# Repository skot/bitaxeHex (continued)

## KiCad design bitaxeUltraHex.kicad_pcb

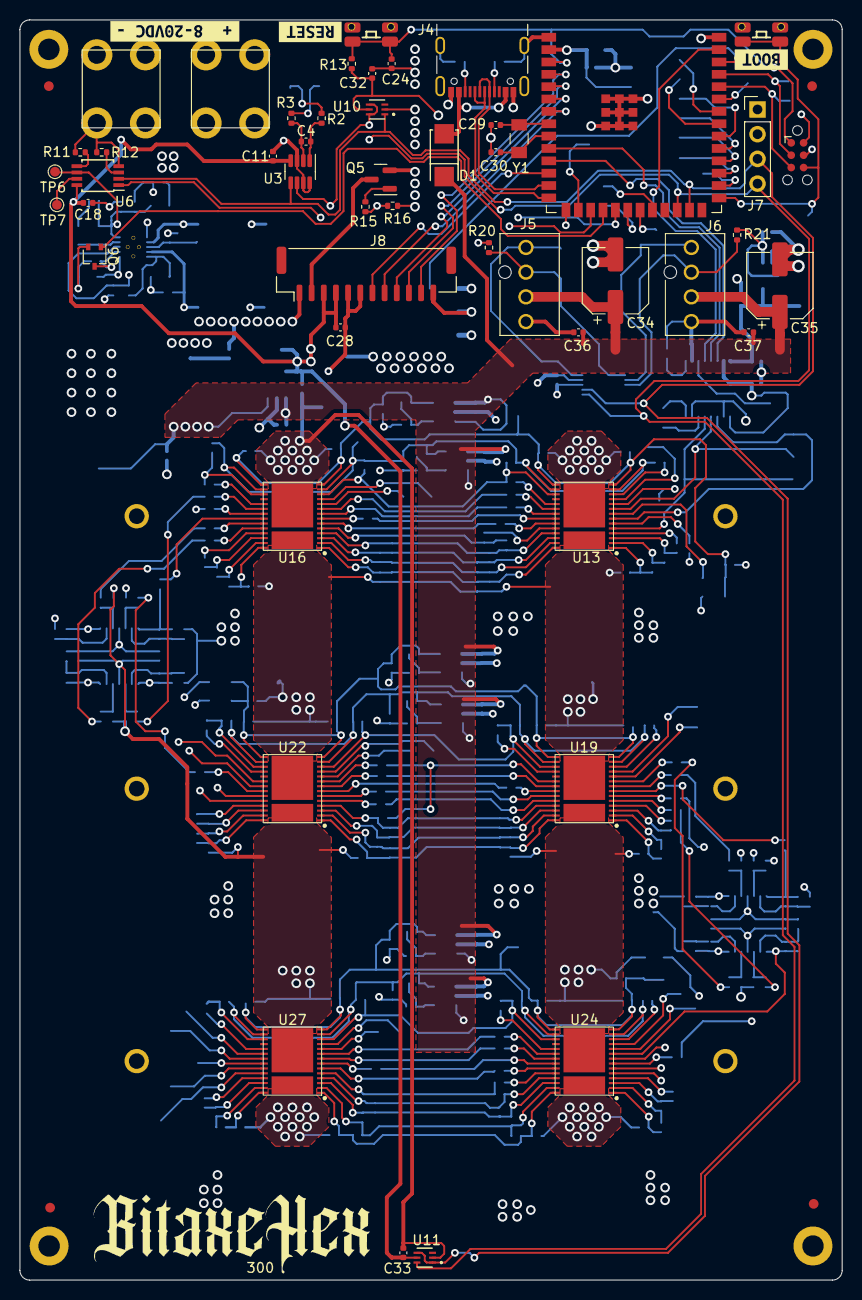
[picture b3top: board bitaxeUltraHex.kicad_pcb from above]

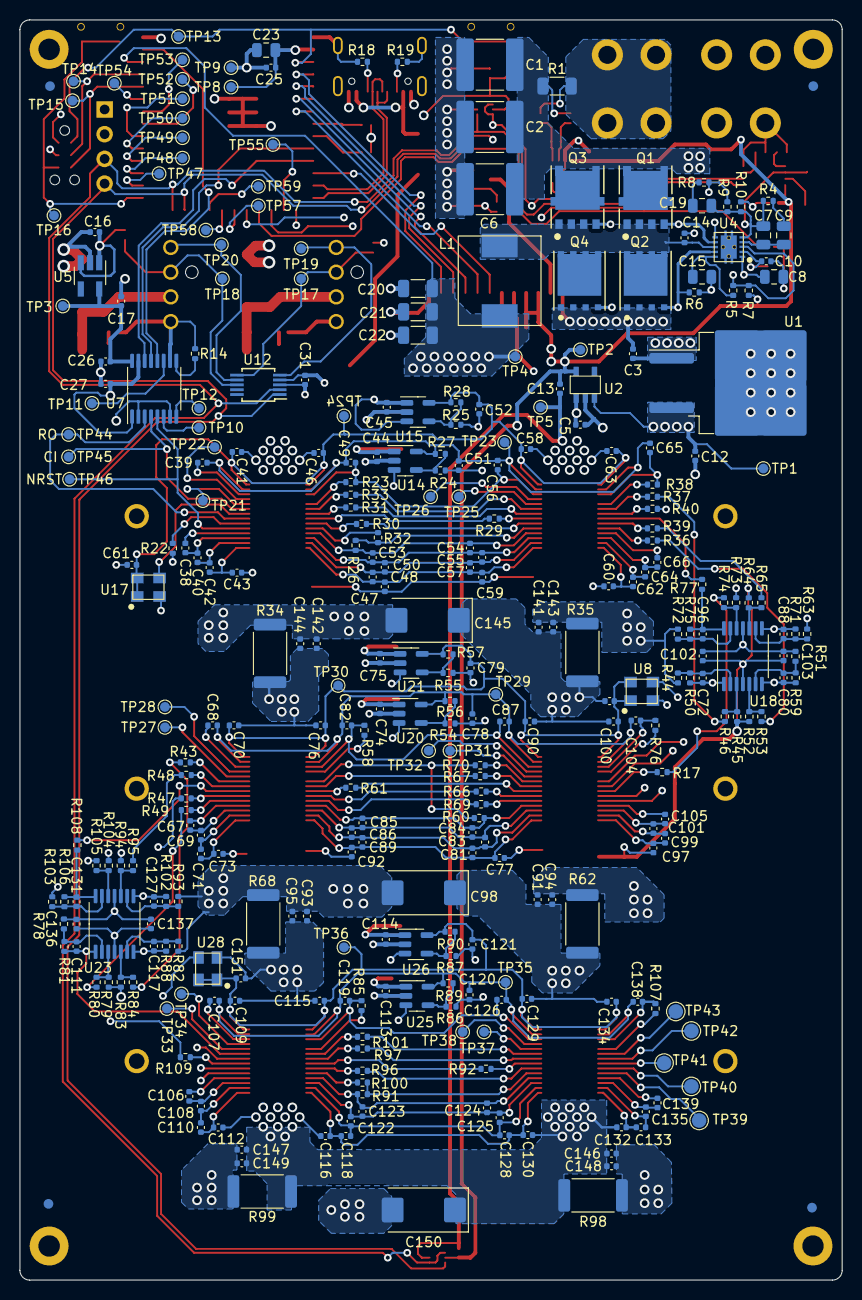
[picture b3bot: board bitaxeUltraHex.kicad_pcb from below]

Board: 4 copper layers, 84.5 x 129.5 mm, 384 parts (318 on the bottom side), 231 nets.

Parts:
C1, C2, C6: 22uF; C_2220_5650Metric
C3: 0.33uF; C_0402_1005Metric
C4: C_0402_1005Metric
C5, C11, C13, C16, C17, C18, C24, C38, C39, C40, C41, C42, C43, C46, C47, C48, C49, C50, C51, C52, C53, C54, C55, C56, C57, C58, C59, C60, C62, C63, C64, C65, C66, C67, C68, C69, C70, C71, C72, C73, C76, C77, C78, C79, C80, C81, C82, C83, C84, C85, C86, C87, C88, C89, C90, C92, C94, C95, C96, C97, C99, C100, C101, C103, C104, C105, C106, C107, C108, C109, C110, C111, C112, C115, C116, C117, C118, C119, C120, C121, C122, C123, C124, C125, C126, C127, C128, C129, C130, C131, C132, C133, C134, C135, C137, C138, C139, C143, C144, C148, C149: 1uF; C_0402_1005Metric
C7: 270pF; C_0805_2012Metric
C8: 1uF; C_0805_2012Metric
C9: 5.6nF; C_0805_2012Metric
C10: 3.3nF; C_0402_1005Metric
C12, C14, C25, C28, C44, C45, C61, C74, C75, C91, C93, C102, C113, C114, C136, C140, C141, C142, C146, C147, C151: 0.1uF; C_0402_1005Metric
C15: 4.7uF; C_0805_2012Metric
C19: 680pF; C_0805_2012Metric
C20, C21, C22: 10uF; C_1206_3216Metric
C23: 10uF; C_0805_2012Metric
C26, C27, C31, C32, C33, C36, C37: 311-3342-1-ND; C_0402_1005Metric
C29, C30: 6.8pF; C_0402_1005Metric
C34, C35: 220uF; CP_Elec_6.3x7.7
C98, C145, C150: 330uF; CP_EIA-7343-31_Kemet-D_Pad2.25x2.55mm_HandSolder
D1: SS310; SMA_L4.3-W2.6-LS5.2-RD
FID1, FID2, FID3, FID4, FID5, FID6, FID7, FID8: Fiducial; Fiducial_1mm_Mask2mm
H1, H2, H3, H4: MountingHole; 4mm_mounting
H5, H6, H7, H8, H9, H10: HeatsinkMountingHole; 2.5mm_mounting
J1: Screw Terminal; 7770-screw-terminal
J2: Conn_01x01; 7770-screw-terminal
J3: TC2030-IDC; Tag-Connect_TC2030-IDC-NL_2x03_P1.27mm_Vertical
J4: USB_C_Receptacle_USB2.0; USB_C_Receptacle_GCT_USB4105-xx-A_16P_TopMnt_Horizontal
J5, J6: Conn_01x04; 470531000
J7: Conn_01x04; PinHeader_1x04_P2.54mm_Vertical
J8: ST7789 176x320; JST_GH_BM12B-GHS-TBT_1x12-1MP_P1.25mm_Vertical
L1: 470nH; 744373580047
Q1, Q3: NTMFS5C673NLT1G
Q2, Q4: CSD17577Q5A
Q5: BSS123; SOT-23
Q6: 2N7002K; SOT-323_SC-70
R1: 2m; R_1206_3216Metric
R2, R3, R32, R36, R43, R70, R100: 0; R_0402_1005Metric
R4: 1.33k; R_0402_1005Metric
R5: 100k; R_0402_1005Metric
R6: 6.49k; R_0402_1005Metric
R7, R9, R13, R16, R22: 10k; R_0402_1005Metric
R8: 487; R_0402_1005Metric
R10: 1.54k; R_0402_1005Metric
R11: 80k; R_0402_1005Metric
R12: DNP; R_0402_1005Metric
R14: 20K; R_0402_1005Metric
R15: 1k; R_0402_1005Metric
R17, R29, R30, R31, R33, R37, R39, R40, R47, R48, R49, R61, R66, R67, R69, R92, R96, R97, R101, R109: 33; R_0402_1005Metric
R18, R19: 5.1k; R_0402_1005Metric
R20, R21: 5.6k; R_0402_1005Metric
R23, R26, R38, R58, R60, R76, R85, R91, R107: 6.8k; R_0402_1005Metric
R24, R54, R86: 309K; R_0402_1005Metric
R25, R55, R87: 130K; R_0402_1005Metric
R27, R28, R56, R57, R89, R90: 182K; R_0402_1005Metric
R34, R35, R62, R68, R98, R99: 1; R_2512_6332Metric
R44, R45, R50, R51, R59, R63, R71, R72, R75, R77, R78, R81, R82, R88, R93, R102, R103, R106, R108: 1K; R_0402_1005Metric
R46, R52, R53, R64, R65, R73, R74, R79, R80, R83, R84, R94, R95, R104, R105: 10K; R_0402_1005Metric
SW1, SW2: EVQ-9P701P; EVQ9P701P-switch
TP1, TP2, TP3, TP4, TP5, TP6, TP7, TP8, TP9, TP10, TP11, TP12, TP13, TP14, TP15, TP16, TP17, TP18, TP19, TP20, TP21, TP22, TP23, TP24, TP25, TP26, TP27, TP28, TP29, TP30, TP31, TP32, TP33, TP34, TP35, TP36, TP37, TP38, TP44, TP45, TP46, TP47, TP48, TP49, TP50, TP51, TP52, TP53, TP54, TP55, TP57, TP58, TP59: TestPoint; TestPoint_Pad_D1.0mm
TP39, TP40, TP41, TP42, TP43: TestPoint; TestPoint_Pad_D1.5mm
U1: uA7805; TO-263-2
U2: RT9080-33GJ5
U3: INA219AIDCNR; SOT-23-8
U4: TPS40305
U5: MIC5504; SOT-23-5_HandSoldering
U6: DS4432U+; TSSOP-8_3x3mm_P0.65mm
U7: SN74AVC4T774; TSSOP-16_4.4x5mm_P0.65mm
U8, U17, U28: 25MHz; O 25,0-JO32-B-1V3-1-T1-LF
U9: ESP32-S3-WROOM-1; ESP32-S3-WROOM-1U
U10, U11: TMP1075; SOT5X3-6_DRL_TEX
U12: EMC2302; MSOP-10_3x3mm_P0.5mm
U13, U16, U24, U27: BM1366_mode1; BM1366
U14, U15, U20, U21, U25, U26: ADP171AUJ-R7; TSOT-23-5
U18, U23: TLV3544; TSSOP-14_4.4x5mm_P0.65mm
U19, U22: BM1366_mode0; BM1366
Y1: 32.768kHz; SC32S-7PF20PPM
kibuzzard-65356D4E: G***; kibuzzard-65356D4E
kibuzzard-65356D5C: G***; kibuzzard-65356D5C
kibuzzard-65356D44: G***; kibuzzard-65356D44

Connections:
/1V8: C17.1, C26.2, TP3.1, U5.5 (VOUT), U7.16 (VCCA)
/3V3: C11.1, C13.1, C16.1, C18.1, C23.1, C25.1, C27.1, C28.1, C31.1, C32.1, C33.1, J3.2, J7.2, J8.3, J8.4, R7.1, R13.1, R20.2, R21.2, TP2.1, TP8.1, U2.5 (VOUT), U3.4 (VS), U5.1 (VIN), U5.3 (EN), U6.8 (VCC), U7.1 (DIR1), U7.15 (VCCB), U9.2 (3V3), U9.15 (GPIO3/TOUCH3/ADC1_CH2*), U10.5 (V+), U11.5 (V+), U12.3 (VDD)
/5V: C5.1, C12.1, C34.1, C35.1, C36.1, C37.1, C44.1, C45.1, C74.1, C75.1, C113.1, C114.1, D1.1, J5.2, J6.2, TP1.1, U1.3 (OUT), U2.1 (VIN), U2.3 (EN), U14.1 (VIN), U14.3 (EN), U15.1 (VIN), U15.3 (EN), U20.1 (VIN), U20.3 (EN), U21.1 (VIN), U21.3 (EN), U25.1 (VIN), U25.3 (EN), U26.1 (VIN), U26.3 (EN)
/BM1366-1/0V8: C39.2, C49.2, C51.1, C56.2, C65.1, R27.1, TP23.1, U13.13 (VDDIO_08_0), U13.16 (VDDIO_08_1), U14.5 (VOUT), U16.13 (VDDIO_08_0), U16.16 (VDDIO_08_1)
/BM1366-1/1V2: C41.1, C46.1, C52.1, C58.1, C61.2, C63.1, R28.1, TP24.1, U13.14 (VDDIO_18_0), U13.15 (VDDIO_18_1), U15.5 (VOUT), U16.14 (VDDIO_18_0), U16.15 (VDDIO_18_1), U17.1 (EN), U17.4 (VIN)
/BM1366-1/BI1: R22.2, U13.6 (BI)
/BM1366-1/BO: R39.2, R65.1
/BM1366-1/CLKI1: U13.8 (CLKI), U17.3 (OUT)
/BM1366-1/CO: R37.2, R46.1
/BM1366-1/NRSTO: R36.2, R53.1
/BM1366-1/RI: R77.1, U16.22 (RI)
/BM1366-1/TEMP_N1_1: TP22.1, U13.11 (TEMP_N)
/BM1366-1/TEMP_N2_1: TP26.1, U16.11 (TEMP_N)
/BM1366-1/TEMP_P1_1: TP21.1, U13.10 (TEMP_P)
/BM1366-1/TEMP_P2_1: TP25.1, U16.10 (TEMP_P)
/BM1366-1/VDD1: C43.2, C47.1, C59.2, C60.1, C70.2, C74.2, C75.2, C76.2, C78.2, C79.2, C90.2, C91.2, C93.2, C94.2, C95.2, C98.2, C100.2, C136.1, C137.1, C140.1, C141.1, C142.1, C143.1, C144.1, C145.1, R34.1, R35.1, R54.1, R55.1, R62.2, R68.2, R78.2, R82.2, R93.2, R103.2, R104.1, U8.2 (GND), U13.29 (VDD), U16.29 (VDD), U19.30 (GND), U20.2 (GND), U21.2 (GND), U22.30 (GND), U23.11 (V-)
/BM1366-2/0V8: C68.2, C78.1, C82.2, C87.2, C104.1, R56.1, TP29.1, U19.13 (VDDIO_08_0), U19.16 (VDDIO_08_1), U20.5 (VOUT), U22.13 (VDDIO_08_0), U22.16 (VDDIO_08_1)
/BM1366-2/1V2: C70.1, C76.1, C79.1, C90.1, C100.1, C140.2, R57.1, TP30.1, U8.1 (EN), U8.4 (VIN), U19.14 (VDDIO_18_0), U19.15 (VDDIO_18_1), U21.5 (VOUT), U22.14 (VDDIO_18_0), U22.15 (VDDIO_18_1)
/BM1366-2/BI2: C88.2, R71.1, U18.8, U22.21 (BI)
/BM1366-2/BO: R48.2, R95.1
/BM1366-2/CI2: C72.2, R50.1, U18.1, U22.24 (CI)
/BM1366-2/CLKI1: R40.2, U8.3 (OUT), U22.23 (CLKI)
/BM1366-2/CO: R49.2, R80.1
/BM1366-2/NRSTI2: C80.2, R59.1, U18.7, U22.20 (NRSTI)
/BM1366-2/NRSTO: R43.2, R84.1
/BM1366-2/RI: R108.1, U19.7 (RI)
/BM1366-2/RO2: R17.2, R74.1
/BM1366-2/TEMP_N1_2: TP28.1, U19.11 (TEMP_N)
/BM1366-2/TEMP_N2_2: TP32.1, U22.11 (TEMP_N)
/BM1366-2/TEMP_P1_2: TP27.1, U19.10 (TEMP_P)
/BM1366-2/TEMP_P2_2: TP31.1, U22.10 (TEMP_P)
/BM1366-2/VDD2: C73.2, C77.1, C91.1, C92.2, C93.1, C94.1, C95.1, C97.1, C98.1, C102.2, C103.2, C109.2, C113.2, C114.2, C115.2, C120.2, C121.2, C129.2, C134.2, C146.2, C147.2, C148.2, C149.2, C150.2, C151.1, R45.2, R52.1, R62.1, R64.1, R68.1, R86.1, R87.1, R98.2, R99.2, U18.4 (V+), U19.29 (VDD), U22.29 (VDD), U24.30 (GND), U25.2 (GND), U26.2 (GND), U27.30 (GND), U28.2 (GND)
/BM1366-3/0V8: C107.2, C119.2, C120.1, C126.2, C138.1, R89.1, TP35.1, U24.13 (VDDIO_08_0), U24.16 (VDDIO_08_1), U25.5 (VOUT), U27.13 (VDDIO_08_0), U27.16 (VDDIO_08_1)
/BM1366-3/1V2: C109.1, C115.1, C121.1, C129.1, C134.1, C151.2, R90.1, TP36.1, U24.14 (VDDIO_18_0), U24.15 (VDDIO_18_1), U26.5 (VOUT), U27.14 (VDDIO_18_0), U27.15 (VDDIO_18_1), U28.1 (EN), U28.4 (VIN)
/BM1366-3/BI3: C127.2, R102.1, U23.8, U24.6 (BI)
/BM1366-3/BO3: TP40.1, U27.23 (BO)
/BM1366-3/CI3: C111.2, R81.1, U23.1, U24.9 (CI)
/BM1366-3/CLKI1: R47.2, U24.8 (CLKI), U28.3 (OUT)
/BM1366-3/CLKO3: TP42.1, U27.21 (CLKO)
/BM1366-3/CO3: TP43.1, U27.20 (CO)
/BM1366-3/NRSTI3: C117.2, R88.1, U23.7, U24.5 (NRSTI)
/BM1366-3/NRSTO3: TP39.1, U27.24 (NRSTO)
/BM1366-3/RI3: TP41.1, U27.22 (RI)
/BM1366-3/RO3: R105.1, R109.2
/BM1366-3/TEMP_N1_3: TP34.1, U24.11 (TEMP_N)
/BM1366-3/TEMP_N2_3: TP38.1, U27.11 (TEMP_N)
/BM1366-3/TEMP_P1_3: TP33.1, U24.10 (TEMP_P)
/BM1366-3/TEMP_P2_3: TP37.1, U27.10 (TEMP_P)
/CI: TP45.1, U7.4 (A2), U13.9 (CI)
/ESP32/ASIC_RST: U7.12 (B3), U9.39 (GPIO1/TOUCH1/ADC1_CH0)
/ESP32/EN: C24.1, J3.1, R13.2, SW1.2, TP13.1, U9.3 (EN)
/ESP32/ESP32_RX: U7.14 (B1), U9.11 (GPIO18/U1RXD/ADC2_CH7/CLK_OUT3)
/ESP32/ESP32_TX: U7.13 (B2), U9.10 (GPIO17/U1TXD/ADC2_CH6)
/ESP32/IO0: J3.6, SW2.2, TP16.1, U9.27 (GPIO0/BOOT*)
/ESP32/PWR_EN: Q6.1 (G), U9.18 (GPIO10/TOUCH10/ADC1_CH9/FSPICS0/FSPIIO4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)
/ESP32/P_RX: J3.5, TP15.1, U9.36 (U0RXD/GPIO44/CLK_OUT2)
/ESP32/P_TX: J3.3, TP14.1, U9.37 (U0TXD/GPIO43/CLK_OUT1)
/ESP32/TFT_BLK: R15.1, R16.2, U9.17 (GPIO9/TOUCH9/ADC1_CH8/FSPIHD/SUBSPIHD)
/ESP32/TFT_CS: J8.8, U9.7 (GPIO7/TOUCH7/ADC1_CH6)
/ESP32/TFT_DC: J8.7, U9.12 (GPIO8/TOUCH8/ADC1_CH7/SUBSPICS1)
/ESP32/TFT_RES: J8.11, U9.4 (GPIO4/TOUCH4/ADC1_CH3)
/ESP32/TFT_SCL: J8.9, U9.6 (GPIO6/TOUCH6/ADC1_CH5)
/ESP32/TFT_SDA: J8.10, U9.5 (GPIO5/TOUCH5/ADC1_CH4)
/ESP32/XIN32: C29.1, U9.8 (GPIO15/U0RTS/ADC2_CH4/XTAL_32K_P), Y1.1
/ESP32/XOUT32: C30.1, U9.9 (GPIO16/U0CTS/ADC2_CH5/XTAL_32K_NH5), Y1.2
/Fan/FAN1_PWM: J5.4, TP19.1, U12.5 (PWM1)
/Fan/FAN1_TACH: J5.3, R20.1, TP17.1, U12.6 (TACH1)
/Fan/FAN2_PWM: J6.4, TP20.1, U12.7 (PWM2)
/Fan/FAN2_TACH: J6.3, R21.1, TP18.1, U12.8 (TACH2)
/NRSTI: TP46.1, U7.5 (A3), U13.5 (NRSTI)
/Power/OUT0: C7.2, C19.2, R4.2, R9.2, R10.1, TP6.1, U4.5 (FB), U6.6 (OUT0)
/Power/OUT1: TP7.1, U6.7 (OUT1)
/Power/PGOOD: R5.1, R7.2, U4.3 (PGOOD), U9.19 (GPIO11/TOUCH11/ADC2_CH0/FSPID/FSPIIO5/S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)
/Power/SW: C14.2, L1.1, Q1.1, Q1.2, Q1.3 (S), Q2.5 (D), Q3.1, Q3.2, Q3.3 (S), Q4.5 (D), U4.8 (SW)
/Power/VIN: J1.1, R1.1, R2.1
/Power/VIN_M: C1.1, C2.1, C3.1, C6.1, C8.1, Q1.5 (D), Q3.5 (D), R1.2, R3.1, U1.1 (IN), U4.1 (VDD)
/RO: TP44.1, U7.3 (A1), U13.7 (RO)
/SCL: J7.3, U3.5 (SCL), U6.2 (SCL), U9.25 (GPIO48/SPICLK_N/SUBSPICLK_N_DIFF), U10.1 (SCL), U11.1 (SCL), U11.4 (A0), U12.2 (SMCLK)
/SDA: J7.4, U3.6 (SDA), U6.1 (SDA), U9.24 (GPIO47/SPICLK_P/SUBSPICLK_P_DIFF), U10.4 (A0), U10.6 (SDA), U11.6 (SDA), U12.1 (SMDATA)
/VDD: C20.1, C21.1, C22.1, C112.2, C116.1, C130.2, C132.1, C136.2, C137.2, C146.1, C147.1, C148.1, C149.1, C150.1, L1.2, R8.1, R9.1, R79.1, R83.1, R94.1, R98.1, R99.1, TP4.1, U9.38 (GPIO2/TOUCH2/ADC1_CH1), U23.4 (V+), U24.29 (VDD), U27.29 (VDD)
GND: C1.2, C2.2, C3.2, C5.2, C6.2, C8.2, C10.2, C11.2, C12.2, C13.2, C15.2, C16.2, C17.2, C18.2, C20.2, C21.2, C22.2, C23.2, C24.2, C25.2, C26.1, C27.2, C28.2, C29.2, C30.2, C31.2, C32.2, C33.2, C34.2, C35.2, C36.2, C37.2, C41.2, C44.2, C45.2, C46.2, C51.2, C52.2, C58.2, C61.1, C63.2, C102.1, C103.1, C141.2, C142.2, C143.2, C144.2, C145.2, J2.1, J3.4, J4.A1 (GND), J4.A12 (GND), J4.B1 (GND), J4.B12 (GND), J4.S1 (SHIELD), J5.1, J6.1, J7.1, J8.1, J8.5, J8.6, J8.12, Q2.1, Q2.2, Q2.3 (S), Q4.1, Q4.2, Q4.3 (S), Q5.2 (S), Q6.2 (S), R6.2, R10.2, R11.2, R12.2, R14.1, R16.1, R18.1, R19.1, R22.1, R24.1, R25.1, R34.2, R35.2, R44.2, R51.2, R63.2, R72.2, R73.1, SW1.1, SW2.1, TP5.1, TP9.1, U1.2 (GND), U2.2 (GND), U3.3 (GND), U3.7 (A0), U3.8 (A1), U4.11 (GND), U5.2 (GND), U6.4 (GND), U7.2 (DIR2), U7.7 (DIR3), U7.10 (GND), U9.1 (GND), U9.40 (GND), U9.41 (GND), U10.2 (GND), U11.2 (GND), U12.4 (GND), U13.30 (GND), U14.2 (GND), U15.2 (GND), U16.30 (GND), U17.2 (GND), U18.11 (V-)
unnamed: C9.2, R4.1
unnamed: C19.1, R8.2
unnamed: C38.1, U13.4 (VDD4_0)
unnamed: C53.2, C54.1, R26.1, U13.25 (VDD4_0), U16.4 (VDD4_0)
unnamed: C66.2, U16.25 (VDD4_0)
unnamed: C96.2, R75.1, R77.2, U18.14
unnamed: C106.1, U24.4 (VDD4_0)
unnamed: C123.2, C124.1, R91.1, U24.25 (VDD4_0), U27.4 (VDD4_0)
unnamed: C131.2, R106.1, R108.2, U23.14
unnamed: C139.2, U27.25 (VDD4_0)
unnamed: D1.2, J4.A4 (VBUS), J4.A9 (VBUS), J4.B4 (VBUS), J4.B9 (VBUS)
unnamed: J4.A5 (CC1), R18.2
unnamed: J4.B5 (CC2), R19.2
unnamed: J8.2, Q5.3 (D)
unnamed: Q1.4 (G), Q3.4 (G), U4.7 (HDRV)
unnamed: Q2.4 (G), Q4.4 (G), R6.1, U4.9 (LDRV)
unnamed: Q5.1 (G), R15.2
unnamed: C10.1, Q6.3 (D), U4.2 (EN/SS)
unnamed: C4.1, R2.2, U3.1 (IN+)
unnamed: C4.2, R3.2, U3.2 (IN-)
unnamed: C14.1, U4.6 (BOOT)
unnamed: C15.1, R5.2, U4.10 (BP)
unnamed: C7.1, C9.1, U4.4 (COMP)
unnamed: R11.1, U6.5 (FS0)
unnamed: R12.1, U6.3 (FS1)
unnamed: TP10.1, U7.6 (A4)
unnamed: TP11.1, U7.11 (B4)
unnamed: TP12.1, U7.8 (DIR4)
unnamed: R14.2, U7.9 (OE)
unnamed: TP55.1, U9.16 (*GPIO46)
unnamed: TP57.1, U9.20 (GPIO12/TOUCH12/ADC2_CH1/FSPICLK/FSPIIO6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)
unnamed: TP58.1, U9.21 (GPIO13/TOUCH13/ADC2_CH2/FSPIQ/FSPIIO7/S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)
unnamed: TP59.1, U9.22 (GPIO14/TOUCH14/ADC2_CH3/FSPIWP/FSPIDQS/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)
unnamed: J4.A7 (D-), J4.B7 (D-), U9.13 (GPIO19/U1RTS/ADC2_CH8/CLK_OUT2/USB_D-)
unnamed: J4.A6 (D+), J4.B6 (D+), U9.14 (GPIO20/U1CTS/ADC2_CH9/CLK_OUT1/USB_D+)
unnamed: TP50.1, U9.31 (GPIO38/FSPIWP/SUBSPIWP)
unnamed: TP51.1, U9.32 (MTCK/GPIO39/CLK_OUT3/SUBSPICS1)
unnamed: TP53.1, U9.34 (MTDI/GPIO41/CLK_OUT1)
unnamed: TP52.1, U9.33 (MTDO/GPIO40/CLK_OUT2)
unnamed: TP54.1, U9.35 (MTMS/GPIO42)
unnamed: TP49.1, U9.30 (SPIDQS/GPIO37/FSPIQ/SUBSPIQ)
unnamed: TP47.1, U9.28 (SPIIO6/GPIO35/FSPID/SUBSPID)
unnamed: TP48.1, U9.29 (SPIIO7/GPIO36/FSPICLK/SUBSPICLK)
unnamed: R30.1, U13.23 (BO)
unnamed: R31.1, U13.21 (CLKO)
unnamed: R33.1, U13.20 (CO)
unnamed: C39.1, U13.12 (MODEO)
unnamed: C49.1, C56.1, R23.2, U13.17 (MODE_1), U16.12 (MODEO)
unnamed: R23.1, U13.19 (NC)
unnamed: R32.1, U13.24 (NRSTO)
unnamed: R29.1, U13.22 (RI)
unnamed: C42.2, C43.1, U13.1 (VDD1_0)
unnamed: C47.2, C48.1, C57.2, C59.1, U13.28 (VDD1_1), U16.1 (VDD1_0)
unnamed: C40.2, C42.1, U13.2 (VDD2_0)
unnamed: C48.2, C50.1, C55.2, C57.1, U13.27 (VDD2_1), U16.2 (VDD2_0)
unnamed: C38.2, C40.1, U13.3 (VDD3_0)
unnamed: C50.2, C53.1, C54.2, C55.1, U13.26 (VDD3_1), U16.3 (VDD3_0)
unnamed: R24.2, R27.2, U14.4 (ADJ)
unnamed: R25.2, R28.2, U15.4 (ADJ)
unnamed: R30.2, U16.6 (BI)
unnamed: R39.1, U16.23 (BO)
unnamed: R33.2, U16.9 (CI)
unnamed: R31.2, U16.8 (CLKI)
unnamed: R40.1, U16.21 (CLKO)
unnamed: R37.1, U16.20 (CO)
unnamed: C65.2, R38.2, U16.17 (MODE_1)
unnamed: R38.1, U16.19 (NC)
unnamed: R26.2, R32.2, U16.5 (NRSTI)
unnamed: R36.1, U16.24 (NRSTO)
unnamed: R29.2, U16.7 (RO)
unnamed: C60.2, C62.1, U16.28 (VDD1_1)
unnamed: C62.2, C64.1, U16.27 (VDD2_1)
unnamed: C64.2, C66.1, U16.26 (VDD3_1)
unnamed: R45.1, R46.2, U18.3 (+)
unnamed: C72.1, R44.1, R50.2, U18.2 (-)
unnamed: R52.2, R53.2, U18.5 (+)
unnamed: C80.1, R51.1, R59.2, U18.6 (-)
unnamed: R64.2, R65.2, U18.10 (+)
unnamed: C88.1, R63.1, R71.2, U18.9 (-)
unnamed: R73.2, R74.2, U18.12 (+)
unnamed: C96.1, R72.1, R75.2, U18.13 (-)
unnamed: R67.1, U19.21 (BI)
unnamed: R48.1, U19.8 (BO)
unnamed: R69.1, U19.24 (CI)
unnamed: R66.1, U19.23 (CLKI)
unnamed: R47.1, U19.6 (CLKO)
unnamed: R49.1, U19.5 (CO)
unnamed: C68.1, U19.12 (MODEO)
unnamed: R58.1, U19.18 (MODE_0)
unnamed: C82.1, C87.1, R58.2, U19.17 (MODE_1), U22.12 (MODEO)
unnamed: R60.2, R70.1, U19.20 (NRSTI)
unnamed: R43.1, U19.9 (NRSTO)
unnamed: R61.1, U19.22 (RO)
unnamed: C71.2, C73.1, U19.1 (VDD1_0)
unnamed: C77.2, C81.1, C89.2, C92.1, U19.28 (VDD1_1), U22.1 (VDD1_0)
unnamed: C69.2, C71.1, U19.2 (VDD2_0)
unnamed: C81.2, C83.1, C86.2, C89.1, U19.27 (VDD2_1), U22.2 (VDD2_0)
unnamed: C67.2, C69.1, U19.3 (VDD3_0)
unnamed: C83.2, C84.1, C85.2, C86.1, U19.26 (VDD3_1), U22.3 (VDD3_0)
unnamed: C67.1, U19.4 (VDD4_0)
unnamed: C84.2, C85.1, R60.1, U19.25 (VDD4_1), U22.4 (VDD4_0)
unnamed: R54.2, R56.2, U20.4 (ADJ)
unnamed: R55.2, R57.2, U21.4 (ADJ)
unnamed: R67.2, U22.8 (BO)
unnamed: R66.2, U22.6 (CLKO)
unnamed: R69.2, U22.5 (CO)
unnamed: R76.2, U22.18 (MODE_0)
unnamed: C104.2, R76.1, U22.17 (MODE_1)
unnamed: R70.2, U22.9 (NRSTO)
unnamed: R61.2, U22.7 (RI)
unnamed: R17.1, U22.22 (RO)
unnamed: C97.2, C99.1, U22.28 (VDD1_1)
unnamed: C99.2, C101.1, U22.27 (VDD2_1)
unnamed: C101.2, C105.1, U22.26 (VDD3_1)
unnamed: C105.2, U22.25 (VDD4_1)
unnamed: R79.2, R80.2, U23.3 (+)
unnamed: C111.1, R78.1, R81.2, U23.2 (-)
unnamed: R83.2, R84.2, U23.5 (+)
unnamed: C117.1, R82.1, R88.2, U23.6 (-)
unnamed: R94.2, R95.2, U23.10 (+)
unnamed: C127.1, R93.1, R102.2, U23.9 (-)
unnamed: R104.2, R105.2, U23.12 (+)
unnamed: C131.1, R103.1, R106.2, U23.13 (-)
unnamed: R96.1, U24.23 (BO)
unnamed: R97.1, U24.21 (CLKO)
unnamed: R101.1, U24.20 (CO)
unnamed: C107.1, U24.12 (MODEO)
unnamed: C119.1, C126.1, R85.2, U24.17 (MODE_1), U27.12 (MODEO)
unnamed: R85.1, U24.19 (NC)
unnamed: R100.1, U24.24 (NRSTO)
unnamed: R92.1, U24.22 (RI)
unnamed: R109.1, U24.7 (RO)
unnamed: C110.2, C112.1, U24.1 (VDD1_0)
unnamed: C116.2, C118.1, C128.2, C130.1, U24.28 (VDD1_1), U27.1 (VDD1_0)
unnamed: C108.2, C110.1, U24.2 (VDD2_0)
unnamed: C118.2, C122.1, C125.2, C128.1, U24.27 (VDD2_1), U27.2 (VDD2_0)
unnamed: C106.2, C108.1, U24.3 (VDD3_0)
unnamed: C122.2, C123.1, C124.2, C125.1, U24.26 (VDD3_1), U27.3 (VDD3_0)
unnamed: R86.2, R89.2, U25.4 (ADJ)
unnamed: R87.2, R90.2, U26.4 (ADJ)
unnamed: R96.2, U27.6 (BI)
unnamed: R101.2, U27.9 (CI)
unnamed: R97.2, U27.8 (CLKI)
unnamed: C138.2, R107.2, U27.17 (MODE_1)
unnamed: R107.1, U27.19 (NC)
unnamed: R91.2, R100.2, U27.5 (NRSTI)
unnamed: R92.2, U27.7 (RO)
unnamed: C132.2, C133.1, U27.28 (VDD1_1)
unnamed: C133.2, C135.1, U27.27 (VDD2_1)
unnamed: C135.2, C139.1, U27.26 (VDD3_1)

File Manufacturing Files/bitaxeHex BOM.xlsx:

Qty | Ref Des | Value | DK | Manufacturer | PARTNO | DNP
3 | C1, C2, C6 | 22uF | 445-1655-1-ND |  | CKG57NX5R1H226M500JH
1 | C3 | 0.33uF | 490-GRM155R61J334ME01JCT-ND |  | GRM155R61J334ME01J
1 | C4 | 1uF | 587-5514-1-ND |  | EMK105BJ105MV-F | DNP
101 | C5, C11, C13, C16, C17, C18, C24, C38, C39, C40, C41, C42, C43, C46, C47, C48, 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 | 1uF | 587-5514-1-ND |  | EMK105BJ105MV-F
1 | C7 | 270pF | 399-C0805C271J5GAC7800CT-ND |  | C0805C271J5GAC7800
1 | C8 | 1uF | 1276-6471-1-ND |  | CL21B105KOFNNNG
1 | C9 | 5600pF | 445-6944-1-ND |  | CGA4C2C0G1H562J060AA
1 | C10 | 3300pF | 1276-1552-1-ND |  | CL05B332KB5NNNC
28 | C12, C14, C25, C26, C27, C28, C31, C32, C33, C36, C37, C44, C45, C61, C74, C75,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 | 0.1uF | 1292-1639-1-ND |  | 0402X104K100CT
1 | C15 | 4.7uF | 490-14466-1-ND |  | GRM21BR71C475KE51L
1 | C19 | 680pF | 311-1126-1-ND |  | CC0805KRX7R9BB681
3 | C20, C21, C22 | 10uF | 1276-6641-1-ND |  | CL31B106MOHNNNE
1 | C23 | 10uF | 1276-1096-1-ND |  | CL21A106KOQNNNE
2 | C29, C30 | 6.8pF | 399-C0402C689C5GAC7867CT-ND |  | C0402C689C5GAC7867
2 | C34, C35 | 220uF | 732-8422-1-ND |  | 865080345012
3 | C98, C145, C150 | 330uF | 718-1028-1-ND |  | 293D337X9010E2TE3
1 | D1 | SS310 | SK310A-LTPMSCT-ND |  | SK310A-LTP
1 | J1 | Screw Terminal | 36-7770-ND |  | 36-7770
1 | J2 | Conn_01x01 | A100886CT-ND |  | 63862-1
1 | J4 | USB_C_Receptacle_USB2.0 | 2073-USB4105-GF-ACT-ND |  | USB4105-GF-A
2 | J5, J6 | Conn_01x04 | WM4330-ND |  | 0470531000
1 | J8 | ST7789 176x320 | 455-BM12B-GHS-TBTCT-ND |  | BM12B-GHS-TBT
1 | L1 | 470nH | 732-7221-1-ND |  | 744373580047
2 | Q1, Q3 | NTMFS5C673NLT1G | NTMFS5C673NLT1GOSCT-ND |  | NTMFS5C673NLT1G
2 | Q2, Q4 | CSD17577Q5A | 296-39996-1-ND |  | CSD17577Q5A
1 | Q5 | BSS123 | 4530-BSS123CT-ND |  | BSS123
1 | Q6 | 2N7002K | 2N7002KWCT-ND |  | 2N7002KW
1 | R1 | 2m | 13-PA1206FRE7W0R002ZCT-ND |  | PA1206FRE7W0R002Z
5 | R2, R3, R36, R43, R70 | 0 | 311-0.0JRCT-ND |  | RC0402JR-070RL
1 | R4 | 1.33k | 311-1.33KLRCT-ND |  | RC0402FR-071K33L
1 | R5 | 100k | 311-100KJRCT-ND |  | RC0402JR-07100KL | DNP
1 | R6 | 6.49k | 311-6.49KLRCT-ND |  | RC0402FR-076K49L
20 | R7, R9, R13, R16, R22, R46, R52, R53, R64, R65, R73, R74, R79, R80, R83, R84, R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 | 10k | 311-10KJRCT-ND |  | RC0402JR-0710KL
1 | R8 | 487 | YAG2373CT-ND |  | RC0402FR-07487RL
1 | R10 | 1.54k | YAG3040CT-ND |  | RC0402FR-071K54L
1 | R11 | 80k | 311-80.6KLRCT-ND |  | RC0402FR-0780K6L
1 | R12 | DNP |  |  |  | DNP
1 | R14 | 20K | 311-20.0KLRCT-ND |  | RC0402FR-0720KL
20 | R15, R44, R45, R50, R51, R59, R63, R71, R72, R75, R77, R78, R81, R82, R88, R93,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 | 1k | 311-1.00KLRCT-ND |  | RC0402FR-071KL
20 | R17, R29, R30, R31, R33, R37, R39, R40, R47, R48, R49, R61, R66, R67, R69, R92,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 | 33 | 311-33.0LRCT-ND |  | RC0402FR-0733RL
2 | R18, R19 | 5.1k | 13-RC0402FR-135K1LCT-ND |  | RC0402FR-135K1L
2 | R20, R21 | 5.6k | 13-RC0402FR-135K6LCT-ND |  | RC0402FR-135K6L
6 | R23, R32, R38, R41, R42, R58 | 33 | 311-33.0LRCT-ND |  | RC0402FR-0733RL | DNP
3 | R24, R54, R86 | 309k 1% | YAG3108CT-ND |  | RC0402FR-07309KL
3 | R25, R55, R87 | 69.8k 1% | YAG3216CT-ND |  | RC0402FR-0769K8L
3 | R26, R60, R91 | 2k | YAG2303CT-ND |  | RT0402BRD072KL
6 | R27, R28, R56, R57, R89, R90 | 182k 1% | YAG3015CT-ND |  | RC0402FR-07182KL
6 | R34, R35, R62, R68, R98, R99 | 1 | 118-CR2512-F/-1R00ELFCT-ND |  | CR2512-F/-1R00ELF
2 | SW1, SW2 | EVQ-9P701P | P19095CT-ND | G-Switch(品赞) | EVQ-9P701P
1 | U1 | uA7805 | 296-20796-1-ND |  | UA7805CKTTR
1 | U2 | RT9080-33GJ5 | 1028-1509-1-ND |  | RT9080-33GJ5
1 | U3 | INA219AID | 296-33291-5-ND | TI(德州仪器) | INA219AID
1 | U4 | TPS40305 | 296-37445-1-ND |  | TPS40305DRCR
1 | U5 | MIC5504 | 576-4879-1-ND |  | MIC5504-1.8YM5-TR
1 | U6 | DS4432U+ | DS4432U+-ND |  | DS4432U+
1 | U7 | SN74AVC4T774 | 296-24739-1-ND |  | SN74AVC4T774PWR
3 | U8, U17, U28 | 25MHz | 1908-O250-JO32-B-1V3-1-T1-LFCT-ND |  | O 25,0-JO32-B-1V3-1-T1-LF
1 | U9 | ESP32-S3-WROOM-1 | 1965-ESP32-S3-WROOM-1U-N16R8CT-ND |  | ESP32-S3-WROOM-1U-N16R8
1 | U10 | TMP1075 | 296-TMP1075NDRLRCT-ND |  | TMP1075NDRLR
1 | U11 | TMP1075 | 296-TMP1075NDRLRCT-ND |  | TMP1075NDRLR
1 | U12 | EMC2302 | EMC2302-2-AIZL-CT-ND |  | EMC2302-2-AIZL-TR
2 | U13, U24 | BM1366_mode1
6 | U14, U15, U20, U21, U25, U26 | ADP171AUJ-R7 | 505-ADP171AUJZ-R7CT-ND |  | ADP171AUJZ-R7
2 | U16, U27 | BM1366_mode1
2 | U18, U23 | TLV3544 | 296-45352-1-ND |  | TLV3544IPWR
1 | U19 | BM1366_mode0
1 | U22 | BM1366_mode0
1 | Y1 | 32.768kHz | 728-1074-1-ND |  | SC32S-7PF20PPM

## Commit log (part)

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2023-08-22 renamed hex to ultraHex
2023-08-31 update with BM1366
2023-09-01 cleanup parts and symbol libraries. added TMP1075
2023-09-01 added EMC2302
2023-09-01 added DK and PARTNO for the fan controller and temp sensors
2023-09-11 moved all custom symbols and footprints to the bitaxe library
2023-09-11 very rough sorting and placement
2023-09-12 more rough layout work
2023-09-12 cleanup
2023-09-12 flip center asic pads
2023-09-12 alignment
2023-09-14 test file for pushing to repo
2023-09-14 Replace reference voltage regulators with new one
2023-09-15 switch voltage reference regulators to ADP170, reannotate
2023-09-15 arrange components around voltage regulators
2023-09-15 Rough draft parts placement
2023-09-15 changed USB connector to USB C. updated display.
2023-09-15 added enclosure edge cuts. added heatsink outline. changed the two middle voltage domain ASICs to mode 0 so the data lines can snake through all 6 chips.
2023-09-15 value label cleanup
2023-09-22 add level translator circuits to ASIC communications
2023-09-23 Update temperature sensors, start deep review
2023-09-24 add 1v8 LDO and consolidate voltage level translators
2023-09-25 Resolved all unconnected pins, re-annotated, reviewed for layout
2023-09-27 replace Q5 with BSS123
2023-09-28 Rough parts placement
2023-09-29 shuffle resistors
2023-09-29 more parts placement
2023-09-29 switch power/comms topology to columns and zig-zag
2023-09-29 remove unused libraries
2023-09-29 fixed part numbers and footprints on the buck reg FETs
2023-09-30 add some power planes and do some comms routing
2023-10-01 Arrange the comms voltage level translators
2023-10-01 move power resistors under ASICs
2023-10-01 add screw terminals, replace OLED display with optional connector
2023-10-02 major rework of the power supply section
2023-10-03 add 3D model of screw terminal to footprint
2023-10-04 Revert "More parts placement"
    This reverts commit 19c08c982123baf7c8f78aef6401739b38439525.
2023-10-04 more parts placement, switch to ESP32 with external antenna
2023-10-05 nearly final parts placement
2023-10-09 Routing of front end ESP32, power supply, fan controller, level translator, and programming connector
2023-10-10 shuffle resistors on RI/RO, more routing on ASICs
2023-10-12 finish routing communications
2023-10-13 add oscillators, large bypass caps, start routing reference voltages
2023-10-16 Finished routing stage 1
2023-10-16 added some models and regenerated the board render
2023-10-16 update ESP32 3d model
2023-10-16 added some DK part numbers
2023-10-17 Add ESP32 testpoints, fix all DRC errors
2023-10-19 added PWR_EN transistor
2023-10-19 switched PWR_EN to GPIO10 so that we can match this up better with ultra-v1.2
2023-10-19 removed external libraries from project settings
2023-10-19 cleaned up some DRC warnings
2023-10-22 added fiducials
2023-10-22 changed version to 300
2023-10-22 re added mounting holes and heatsink mounting holes.
2023-10-22 BOM mostly completed
2023-10-22 added BOM, schematic PDF, position file and candidate gerbers
2023-10-23 add heatsink to library and PCB render
2023-10-23 rename project file to "bitaxeHex". remove old gerbers
2023-10-23 pull in updated TPS40305 footprint
2023-10-23 link heatsink to schematic and re-link heatsink mounting holes :P
2023-10-23 silkscreen cleanup
2023-10-24 fix D1 part numbers
2023-10-24 U10,U11 BOM fix
2023-10-24 a little less paste on the BM1366 power pads
2023-10-25 sorting out new info on the BM1366 pinouts
2023-10-26 routed 1366 changes
2023-10-31 Generate gerbers/stencil files
2023-10-31 add readme file to gerbers
2023-10-31 generate final schematic PDF for version 300
2023-11-01 combine stencils into the main gerber directory and zip file. Add readme file to gerbers
2023-11-01 add hex-display adapter board
2023-11-01 add readme file
2023-11-01 fix footprint on U3, generate new gerbers
2023-11-03 fix copper power plane to ASIC to cover more vias
2023-11-03 add pcb design for power plane fix
2023-11-03 Fix some part numbers in the BOM
2023-11-03 Fix BOM to reflect part number changes
2023-11-04 add option for 1.5V ASIC Vref
2023-11-05 add note to specify resistor value for 1.8V reference voltage
2023-11-06 updated 1V2 to 1V8 and updated the BOM
2023-11-09 Fix package for C15, C20, C21, C22 on schematic and on BOM. PCB footprints were already correct
2023-11-10 change R5 to DNP on schematic and BOM
2023-11-10 change 1 ohm power resistors to 2 watt parts, changed schematic and BOM
2023-11-19 mounting holes and fiducials
2023-11-20 fix mounting holes size/spacing, add pullup to PWR_EN signal
2023-11-21 add PWR_EN pullup resistor to PCB layout
2023-11-27 Start working on changelist for v301
2023-12-06 replace TPS40305 buck regulator circuit with LM27402
2023-12-07 finish schematic for power supply section, add part numbers and footprints
2023-12-08 Create footprints for new MOSFETS, start on new power supply
2023-12-09 remove old 5V power supply, prepare footprints for new 5V buck supply, switch fans to 12V
2023-12-09 shuffle capacitors on 5V buck regulator
2023-12-10 power supply work
2023-12-11 finish parts placement for new power supply designs
2023-12-13 More power supply routing
2023-12-14 Yet more power supply routing
2023-12-15 More routing progress
2023-12-16 More routing is done
2023-12-17 Fix level translator negative input
2023-12-17 Finished routing, generate gerbers, edit new BOM for v301
2023-12-18 fix LM27402 footprint
2023-12-18 fix warnings on H3 and H4 mounting holes
2023-12-18 added oscillator 3d
2023-12-18 BOM cleanup
2023-12-18 small schematic cleanup
2023-12-18 screw terminal partno update
2023-12-18 u4 silk
2023-12-18 minor cleanup of silkscreen, traces
2023-12-18 update resistor values for VDD sample divider on schematic and BOM
2023-12-18 fix notes regarding VDD_SAMPLE voltage
2023-12-19 Extend pads on U4 for easier soldering, generate renders of front and back
2023-12-19 Move USB-C connector away from ESP32 to make room for chunky cables
2023-12-19 add updated BOM and new gerber files for v301
2023-12-19 fix rotation of 3D models of power MOSFETs
2023-12-21 adjust some values on the BOM
2023-12-23 switch out reference LDOs for AP7331
2023-12-23 Fix DK partnumber for 402K resistor
2023-12-28 add PDF schematic of v301
2023-12-29 first draft of new power supply schematic using TPS546D24
2023-12-29 remove INA219 power monitor
2023-12-29 5V pullups on fan tachs
2023-12-30 start parts placement for TPS546D24 regulator
2023-12-31 parts placement for new regulator
2024-01-01 lots of power supply routing
2024-01-03 More power supply stuff
2024-01-03 reshuffle power supply planes
2024-01-04 more routing
2024-01-05 Finish initial routing pass
2024-01-05 touch up routing
2024-01-06 connect AGND to GND
2024-01-06 re-annotate all components
2024-01-07 increase size of copper planes, generate final BOM
2024-01-07 final polishing before gerbers
2024-01-07 v302 gerber files
2024-01-08 via organizing on In1. removed islands from In1 and In2
2024-01-08 eliminate more traces on In1, expand copper pour a little more
2024-01-08 generate new gerber files for v302
2024-01-08 fix DRC errors, generate new gerbers
2024-01-08 add PMBus isolation resistors
2024-01-08 zip up latest gerber files
2024-01-10 Set I2C address by choosing ADRSEL resistors
2024-01-12 add heatsink drill guide to 3d directory
2024-01-26 BOM adjustments to R28, R29, config resistors
2024-01-27 change config resistors again
2024-01-30 enable 3d model of U3
2024-02-13 fix notes about dedicated oscillator components
2024-02-14 power resistor values
2024-02-15 update to BOM for config resistors
2024-03-03 update heatsink 3d model
2024-03-03 update readme some more
2024-03-03 Add mounting holes, remove some caps and power resistors
2024-03-03 adjust new mounting hole locations
2024-03-08 updated enclosure AliExpress link
2024-03-09 added Aliexpress 12V PSU
2024-03-11 remove 33R series resistors and other components, add mounting holes
2024-03-14 move fan connector, create new buttons
2024-03-15 update to KiCad8, DNP 32KHz crystal, update BOM
2024-03-21 change buttons to some that are easier to push
2024-03-23 add schematic PDF for v302
2024-03-23 remove old display connector and add BAP, remove USB 5V supply, cleanup routing
2024-03-24 cleanup for v303
2024-03-25 generate BOM and gerber files for v303
2024-03-25 changed trace/space to 8mil. changed default via to 0.3/0.5mm. fixed all DRC errors
2024-03-26 regen 303 gerbers
2024-04-07 changed r value from 10K to 10k, ibom
2024-05-18 add PDF schematic for V303
2024-05-20 update readme with v303 and v304
2024-05-20 swap out electrolytic output capacitor, add XT30 power connector
2024-05-24 fix OP-AMP power supply, connect to GND,+5V
2024-05-24 swap adjustable LDOs for fixed voltage LDOs
2024-05-25 add voltage domain sense signals to the ESP32 ADC
2024-05-25 connect RESET signal in parallel across domains
2024-05-25 revert parallel reset modification back to serial passthrough
2024-05-27 update inductor silkscreen to include line which indicates start of winding orientation
2024-05-31 Update BM1366 footprint to Ultra v206 version
2024-05-31 modify silkscreen for inductors to indicate start of winding orientation
2024-05-31 change temperature sensors to a larger IC package
2024-06-03 More work on the XT30
2024-06-04 arrange power regulator capacitors, finalize I2C pullup resistors
2024-06-04 change rev to 304
2024-06-04 update readme generating manufacturing files
2024-06-05 update readme file
2024-06-06 add silkscreen aids for debugging with more testpoints
2024-06-07 add XT30 3D model
2024-06-09 add resistor dividers to domain voltage sense signals
2024-06-09 Clean up DRC errors vor v304
2024-06-11 fix regulator input caps
2024-06-14 Final cleanup, generate BOM and gerbers
2024-06-18 Added TPS546 heatsink recommendation to readme
2024-07-02 fix airwires from Issue #43
2024-09-16 updated readme with esp-miner-multichip link
